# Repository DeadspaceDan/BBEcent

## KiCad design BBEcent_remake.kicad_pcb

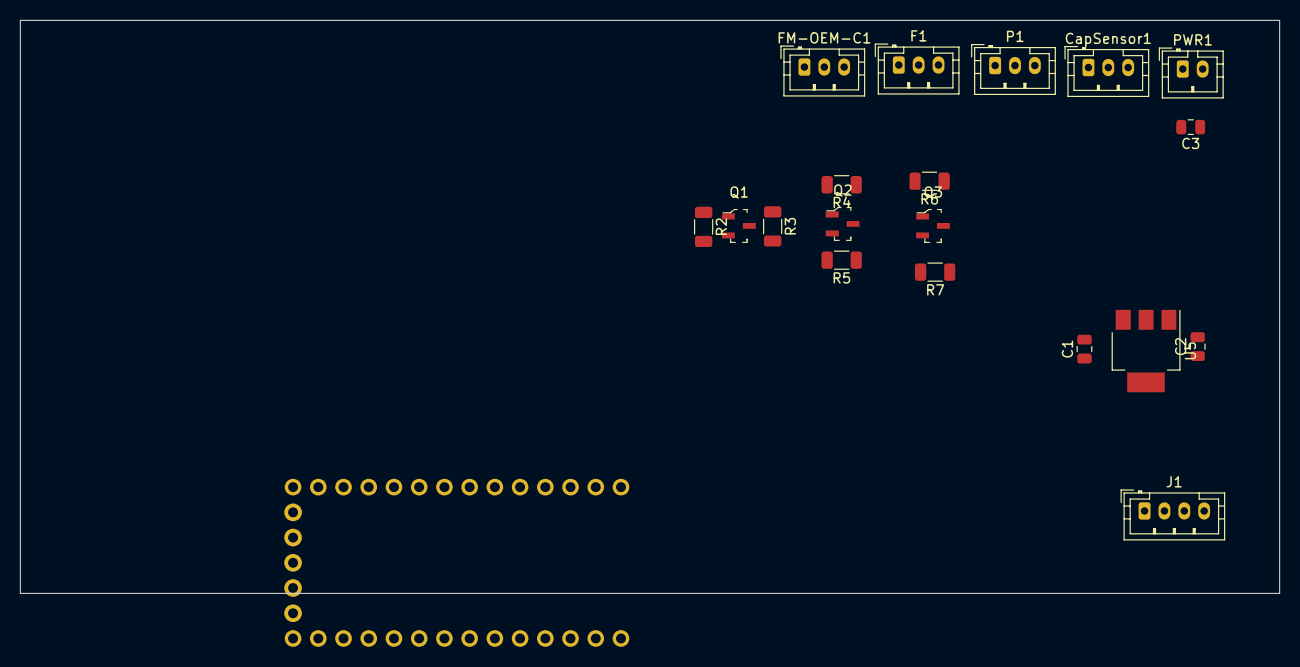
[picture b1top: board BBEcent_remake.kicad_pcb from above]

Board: 2 copper layers, 126.8 x 57.7 mm, 19 parts (0 on the bottom side), 10 nets, no tracks yet.

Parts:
C1, C2: CAP_CERAMIC_0805 4.7uF; C_0805_2012Metric
C3: CAP_CERAMIC_0805 .1uF; C_0805_2012Metric
CapSensor1: Conn_01x03; JST_PH_B3B-PH-K_1x03_P2.00mm_Vertical
F1: Flowmeter_12000781__FHKSC; JST_PH_B3B-PH-K_1x03_P2.00mm_Vertical
FM-OEM-C1: Conn_01x03; JST_PH_B3B-PH-K_1x03_P2.00mm_Vertical
J1: Conn_01x04; JST_PH_B4B-PH-K_1x04_P2.00mm_Vertical
P1: Conn_01x03; JST_PH_B3B-PH-K_1x03_P2.00mm_Vertical
PWR1: Conn_01x02_Male; JST_PH_B2B-PH-K_1x02_P2.00mm_Vertical
Q1, Q2, Q3: SOT-23-3
R2, R3, R4, R5, R6, R7: RESISTOR_0805 10k; R_1206_3216Metric
U5: AP2114HA-3.3 Linear Reg; SOT-223-3_TabPin2

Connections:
+5V: C3.1, PWR1.2
/A3: Q3.1, R6.1
/D11: Q2.1, R4.1
/D13: Q1.1, R2.1
GND: C1.2, C2.2, C3.2, CapSensor1.1, F1.1, FM-OEM-C1.1, J1.1, P1.1, PWR1.1, U5.2 (GND)
HV: C1.1, CapSensor1.2, F1.2, FM-OEM-C1.2, P1.2, Q1.3, Q2.3, Q3.3, R3.2, R5.2, R7.2, U5.1 (VI)
LV: C2.1, Q1.2, Q2.2, Q3.2, R2.2, R4.2, R6.2, U5.3 (VO)
unnamed: F1.3, R5.1
unnamed: FM-OEM-C1.3, R3.1
unnamed: P1.3, R7.1

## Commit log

2022-09-21 Initial Upload of project files
    Initial Upload of project files
